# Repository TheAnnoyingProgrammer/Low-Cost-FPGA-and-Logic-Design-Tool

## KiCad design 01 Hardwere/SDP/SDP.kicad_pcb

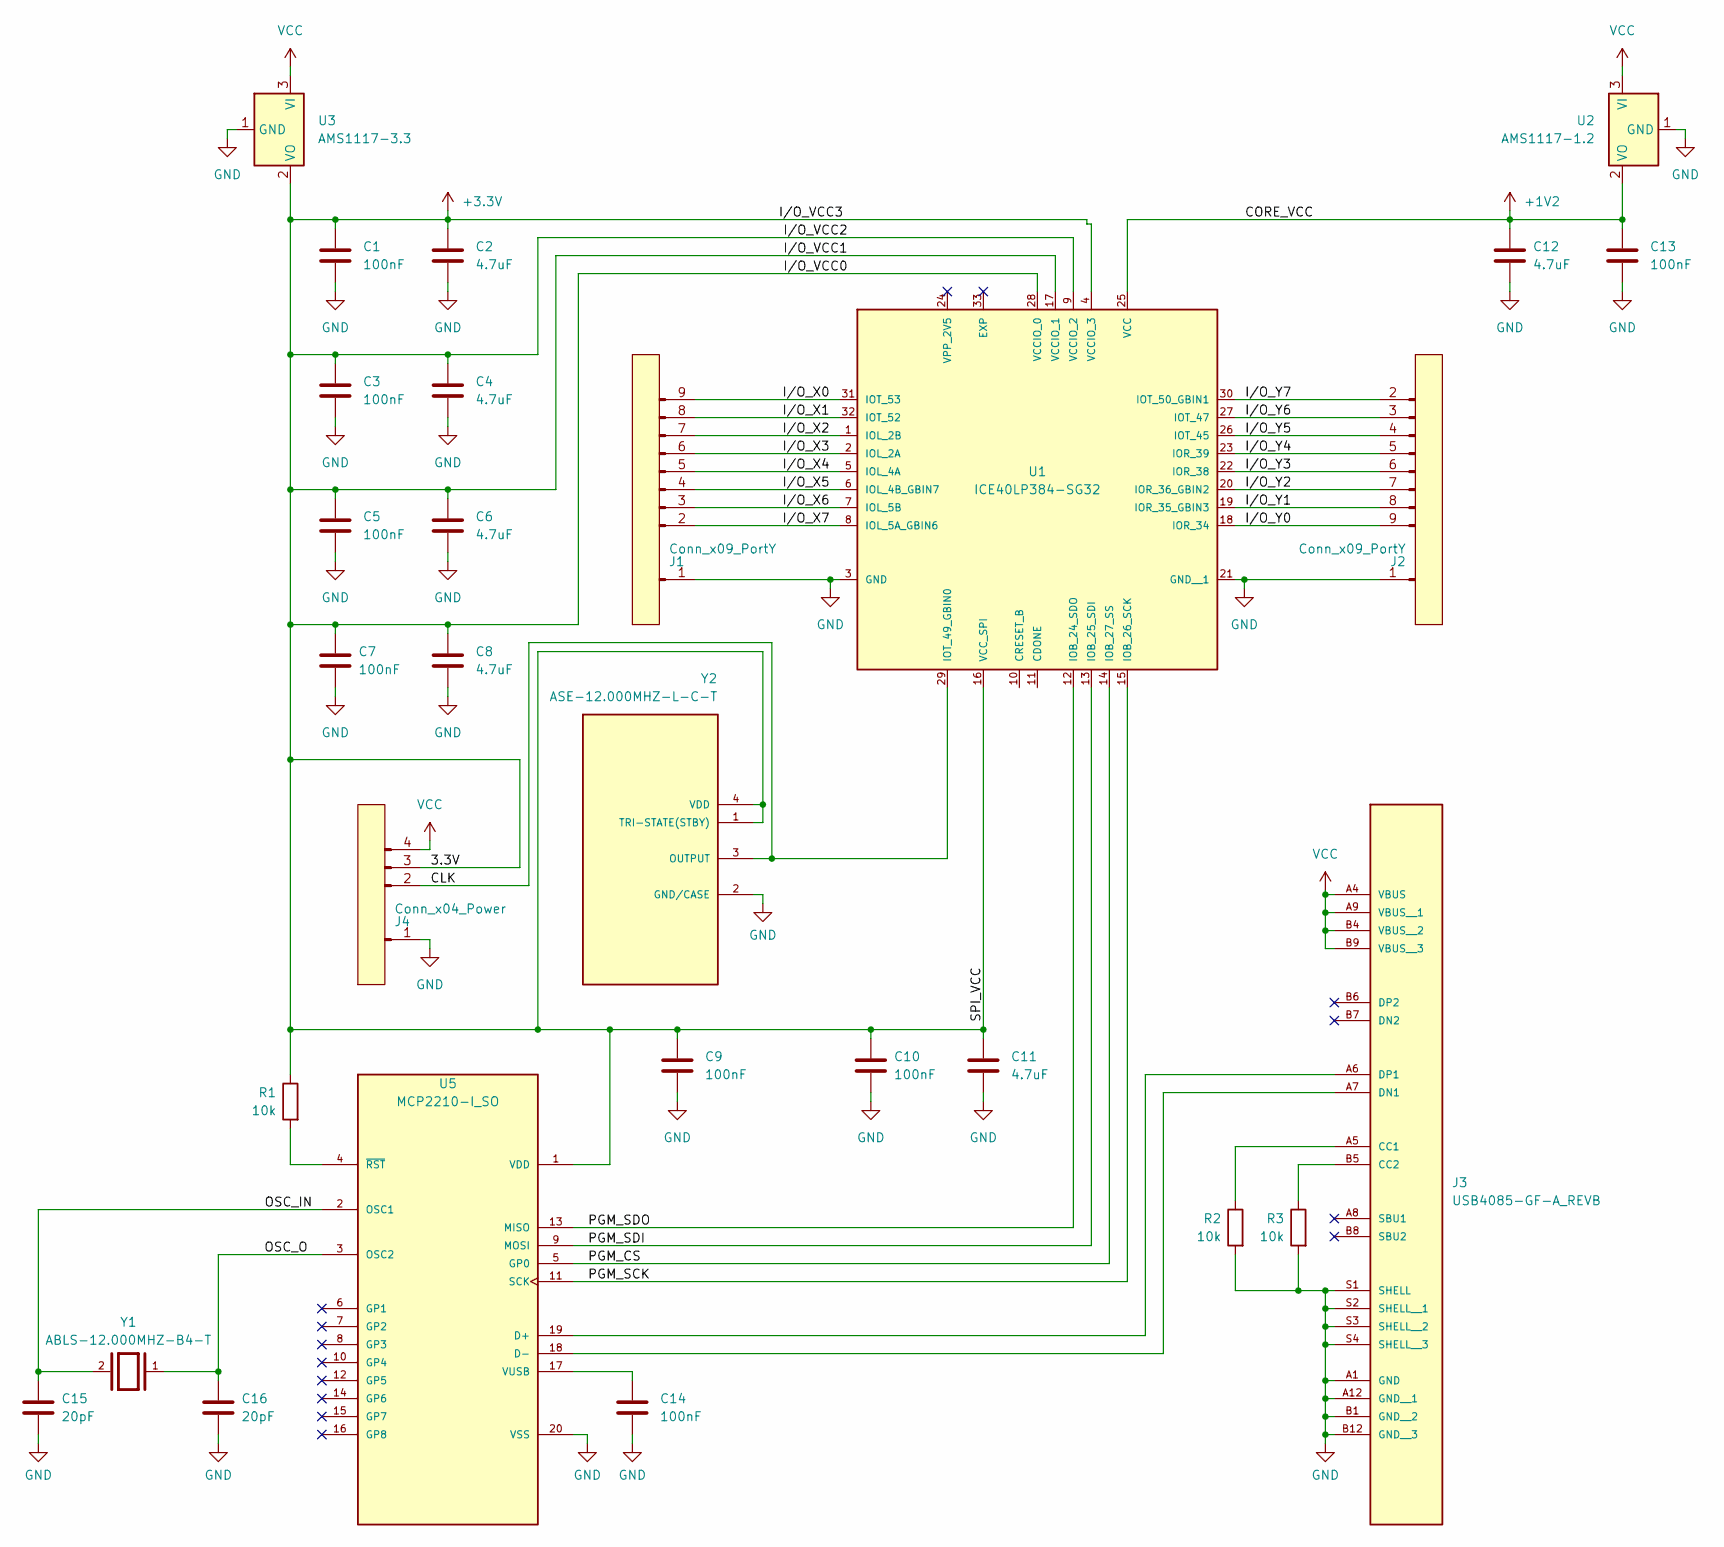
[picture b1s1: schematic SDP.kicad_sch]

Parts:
C1, C3, C5, C7, C9, C10, C13, C14: 100nF; C_0805_2012Metric
C2, C4, C6, C8, C11, C12: 4.7uF; C_0805_2012Metric
C15, C16: 20pF; C_0805_2012Metric
J1, J2: Conn_x09_PortY; PinHeader_1x09_P2.54mm_Vertical
J3: USB4085-GF-A_REVB; USB_C_Receptacle_GCT_USB4085; PARTREV B
J4: Conn_x04_Power; PinHeader_1x04_P2.54mm_Vertical
R1, R2, R3: 10k; R_0805_2012Metric
U1: ICE40LP384-SG32; QFN33P50_500X500X100L40X24T270N
U2: AMS1117-1.2; SOT-223-3_TabPin2
U3: AMS1117-3.3; SOT-223-3_TabPin2
U5: MCP2210-I_SO; SOIC-20W_7.5x12.8mm_P1.27mm; PARTREV C
Y1: ABLS-12.000MHZ-B4-T; XTAL_ABLS-12.000MHZ-B4-T; PARTREV 02.16.2021
Y2: ASE-12.000MHZ-L-C-T; XTAL_ASE-12.000MHZ-L-C-T; PARTREV 02-18-22

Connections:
+1V2: C12.1, C13.1, U1.25 (VCC), U2.2 (VO)
+3.3V: C1.1, C2.1, C3.1, C4.1, C5.1, C6.1, C7.1, C8.1, C9.1, C10.1, C11.1, J4.3, R1.1, U1.4 (VCCIO_3), U1.9 (VCCIO_2), U1.16 (VCC_SPI), U1.17 (VCCIO_1), U1.28 (VCCIO_0), U3.2 (VO), U5.1 (VDD), Y2.1 (TRI-STATE(STBY)), Y2.4 (VDD)
/CLK: J4.2, U1.29 (IOT_49_GBIN0), Y2.3 (OUTPUT)
/I/O_X0: J1.9, U1.31 (IOT_53)
/I/O_X1: J1.8, U1.32 (IOT_52)
/I/O_X2: J1.7, U1.1 (IOL_2B)
/I/O_X3: J1.6, U1.2 (IOL_2A)
/I/O_X4: J1.5, U1.5 (IOL_4A)
/I/O_X5: J1.4, U1.6 (IOL_4B_GBIN7)
/I/O_X6: J1.3, U1.7 (IOL_5B)
/I/O_X7: J1.2, U1.8 (IOL_5A_GBIN6)
/I/O_Y0: J2.9, U1.18 (IOR_34)
/I/O_Y1: J2.8, U1.19 (IOR_35_GBIN3)
/I/O_Y2: J2.7, U1.20 (IOR_36_GBIN2)
/I/O_Y3: J2.6, U1.22 (IOR_38)
/I/O_Y4: J2.5, U1.23 (IOR_39)
/I/O_Y5: J2.4, U1.26 (IOT_45)
/I/O_Y6: J2.3, U1.27 (IOT_47)
/I/O_Y7: J2.2, U1.30 (IOT_50_GBIN1)
/OSC_IN: C15.1, U5.2 (OSC1), Y1.2
/OSC_O: C16.1, U5.3 (OSC2), Y1.1
/PGM_CS: U1.14 (IOB_27_SS), U5.5 (GP0)
/PGM_SCK: U1.15 (IOB_26_SCK), U5.11 (SCK)
/PGM_SDI: U1.13 (IOB_25_SDI), U5.9 (MOSI)
/PGM_SDO: U1.12 (IOB_24_SDO), U5.13 (MISO)
GND: C1.2, C2.2, C3.2, C4.2, C5.2, C6.2, C7.2, C8.2, C9.2, C10.2, C11.2, C12.2, C13.2, C14.2, C15.2, C16.2, J1.1, J2.1, J3.A1 (GND), J3.A12 (GND__1), J3.B1 (GND__2), J3.B12 (GND__3), J3.S1 (SHELL), J3.S2 (SHELL__1), J3.S3 (SHELL__2), J3.S4 (SHELL__3), J3.SH (SHELL), J4.1, R2.2, R3.2, U1.3 (GND), U1.21 (GND__1), U2.1 (GND), U3.1 (GND), U5.20 (VSS), Y2.2 (GND/CASE)
unnamed: J3.A5 (CC1), R2.1
unnamed: J3.B5 (CC2), R3.1
unnamed: J3.A7 (DN1), U5.18 (D-)
unnamed: J3.A6 (DP1), U5.19 (D+)
unnamed: C14.1, U5.17 (VUSB)
unnamed: R1.2, U5.4 (~RST)
VCC: J3.A4 (VBUS), J3.A9 (VBUS__1), J3.B4 (VBUS__2), J3.B9 (VBUS__3), J4.4, U2.3 (VI), U3.3 (VI)

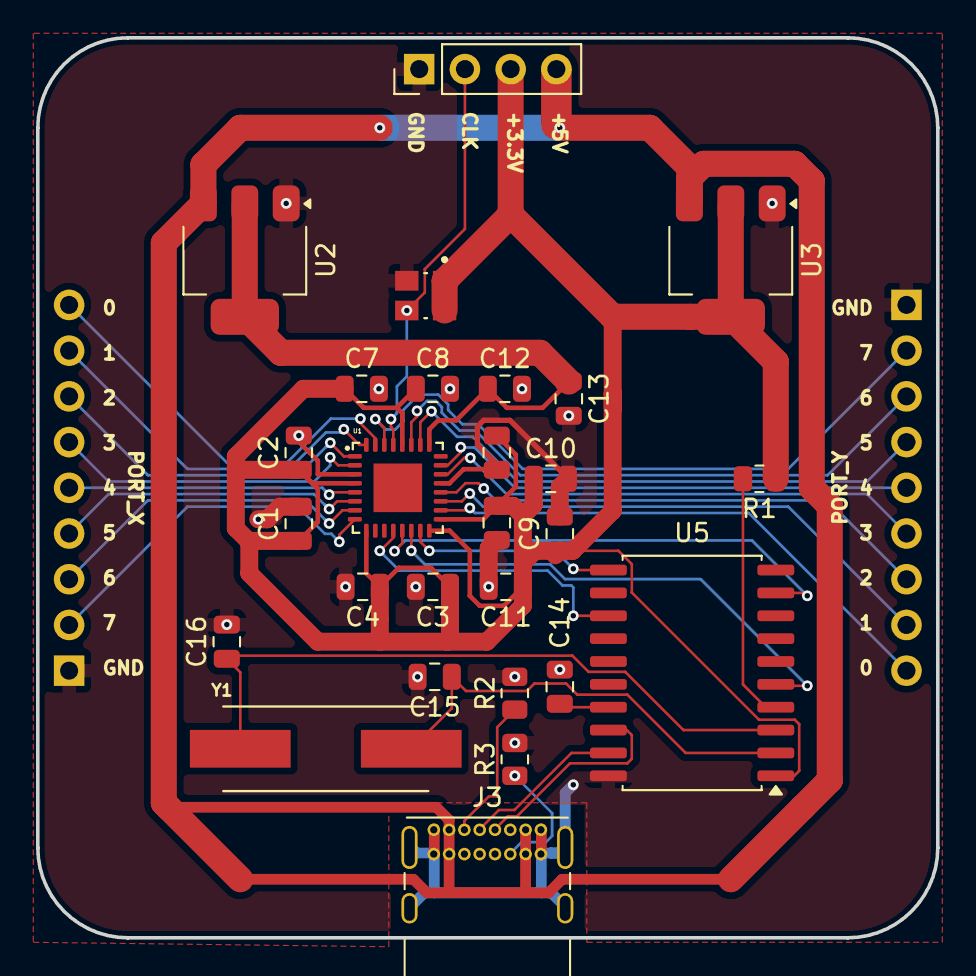
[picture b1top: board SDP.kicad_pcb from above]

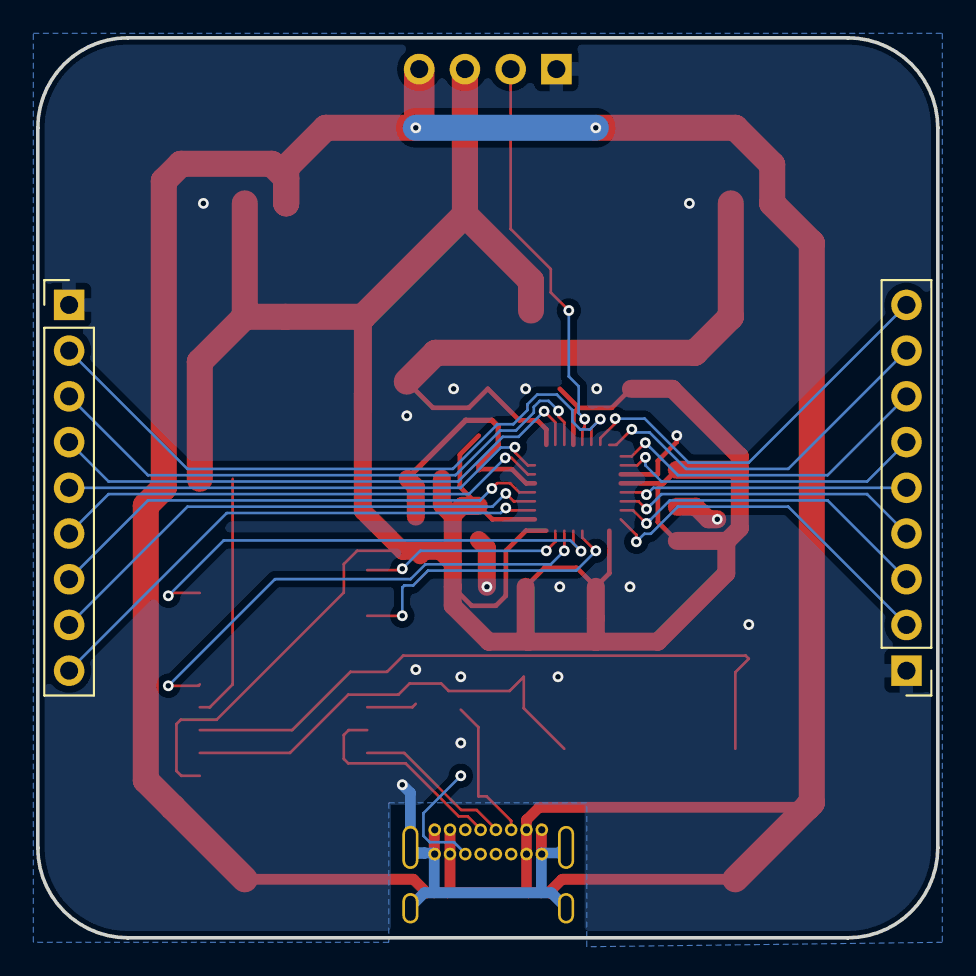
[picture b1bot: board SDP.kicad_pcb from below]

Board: 2 copper layers, 50.0 x 50.0 mm, 29 parts (2 on the bottom side), 33 nets.

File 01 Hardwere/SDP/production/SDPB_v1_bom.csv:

Designator,Footprint,Quantity,Value,LCSC Part #
"C1, C10, C13, C14, C3, C5, C7, C9",0805,8,100nF,
"C11, C12, C2, C4, C6, C8",0805,6,4.7uF,
"C15, C16",0805,2,20pF,
"J1, J2",PinHeader_1x09_P2.54mm_Vertical,2,Conn_x09_PortY,
J3,USB_C_Receptacle_GCT_USB4085,1,USB4085-GF-A_REVB,
J4,PinHeader_1x04_P2.54mm_Vertical,1,Conn_x04_Power,
"R1, R2, R3",0805,3,10k,
U1,QFN33P50_500X500X100L40X24T270N,1,ICE40LP384-SG32,
U2,SOT-223-3_TabPin2,1,AMS1117-1.2,
U3,SOT-223-3_TabPin2,1,AMS1117-3.3,
U5,SOIC-20W_7.5x12.8mm_P1.27mm,1,MCP2210-I_SO,
Y1,XTAL_ABLS-12.000MHZ-B4-T,1,ABLS-12.000MHZ-B4-T,
Y2,XTAL_ASE-12.000MHZ-L-C-T,1,ASE-12.000MHZ-L-C-T,
